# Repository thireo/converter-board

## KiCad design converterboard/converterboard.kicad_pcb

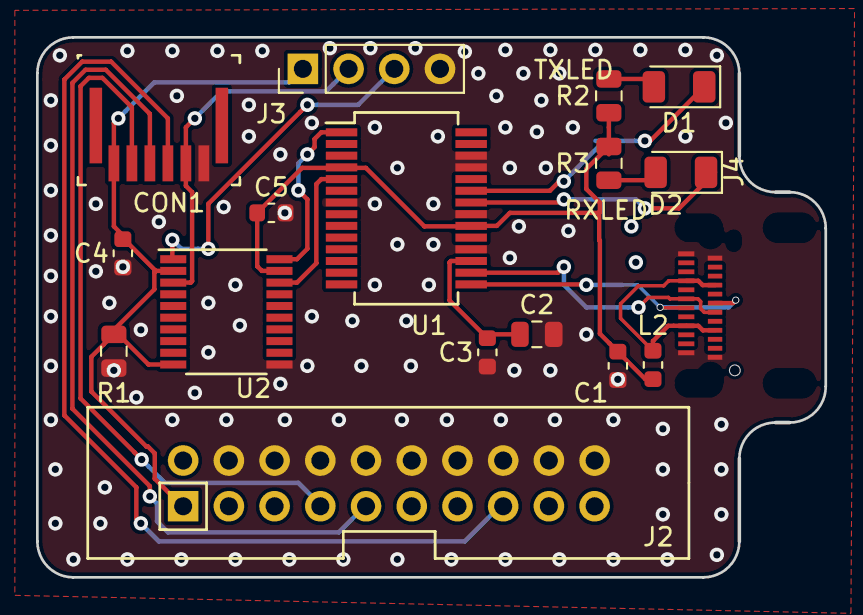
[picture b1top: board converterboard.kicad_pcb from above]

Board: 2 copper layers, 43.8 x 30.0 mm, 17 parts (0 on the bottom side), 18 nets.

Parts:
C1: 10nF; C_0603_1608Metric
C2: 4.7uF; C_0805_2012Metric
C3, C4, C5: 100nF; C_0603_1608Metric
CON1: FPC_6POS; HFW6R_2STE1LF
D1: TXLED; D_1206_3216Metric
D2: RXLED; D_1206_3216Metric
J2: Conn_02x10_Odd_Even; SAM-ICE-Header
J3: Conn_01x04; PinHeader_1x04_P2.54mm_Vertical
J4: USB_C_Receptacle; DX07S024JJ
L2: Ferrite_Bead_Small; L_0603_1608Metric
R1: 10k; R_0805_2012Metric
R2, R3: 100; R_0805_2012Metric
U1: FT232RL; SSOP-28_5.3x10.2mm_P0.65mm
U2: TXB0108PWR; TSSOP-20_4.4x6.5mm_P0.65mm

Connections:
+3V3: C2.1, C3.1, U1.17
/D+: J4.A6, J4.B6, U1.15
/D-: J4.A7, J4.B7, U1.16
/MCU_RESET: CON1.4, J2.15
/RXD: U1.5, U2.18
/SWCLK: CON1.3, J2.9
/SWDIO: CON1.2, J2.7
/TXD: U1.1, U2.20
/UART_RX: J3.3, U2.1
/UART_TX: CON1.5, J3.2, U2.3
GND: C1.2, C2.2, C3.2, C4.2, C5.2, CON1.6, J2.4, J2.6, J2.8, J2.10, J2.12, J2.14, J2.16, J2.18, J2.20, J3.4, J4.A1, J4.A12, J4.B1, J4.B12, R1.1, U1.7, U1.18, U1.21, U1.25, U1.26, U2.11
unnamed: D1.1, U1.23
unnamed: D1.2, R2.2
unnamed: D2.1, U1.22
unnamed: D2.2, R3.2
unnamed: J4.A4, J4.A9, J4.B4, J4.B9, L2.1
VBUS: C1.1, C5.1, L2.2, R2.1, R3.1, U1.4, U1.20, U2.19
VCC: C4.1, CON1.1, J2.1, J3.1, R1.2, U2.2, U2.10

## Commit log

2019-01-17 Initial draft
2019-03-22 HW rev 1+2
2020-08-15 HW rev 3 - Sorry future me.. dunno what I changed. But it might be for the SC2???
